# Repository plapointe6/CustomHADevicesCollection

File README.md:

# Custom Home Assistant devices collection

This repo contain custom IOT devices developped to work with ESP8266/ESP32, MQTT and Home Assistant.

# Required arduino libraries

Most of the devices needs these arduino libraries to work : 
 - https://github.com/plapointe6/EspMQTTClient
 - https://github.com/plapointe6/HAMqttDevice
 - https://github.com/jwrw/ESP_EEPROM

# Required Home Assistant parameters

Home Assistant must be communicating with an MQTT broker.
Here is the suggested configuration in `configuration.yaml` : 

```yaml
mqtt:
  broker: broker ip here
  username: username here
  password: password here
  discovery: true
  discovery_prefix: ha
  birth_message:
    topic: 'ha/status'
    payload: 'online'
    retain: true
  will_message:
    topic: 'ha/status'
    payload: 'offline'
    retain: true
```

# Architecture

These devices take advantages of MQTT discovery in Home Assistant. No manual steps are needed to add these devices in Home Assistant. Also, with the provided code, if something goes wrong (Wifi goes down, MQTT goes down, etc.) everything will reconnect automatically whitout your intervention.

Nothing is retained with MQTT (except for the HA status) and no device use the optimistic mode.

## Message types

There is three messages types when communicating with Home Assitant via MQTT.
- Configuration: these messages register your device into HA with MQTT discovery. all details/config of the device are sent with this message. It is the first thing you have to send to HA.
- State: this contain the current state of the device. For a light, the state will be either "ON" or "OFF".
- Command: this contains a resquest to change the state of the device. Wen receiving that, we do the necessary to update the device (ex: close/open the light) and send back the confirmation to Home Assistant when it's done by sending the new state.
- Attributes: Custom device attributes that can be sent to Home Assitant. These attributes will be displayed in the device card.
- Home assistant status: this is a retained message and contains the state of HA, either "online" or "offline".

## Devices events chronology

1. setup(): initilisations, load the previous state from EEPROM, configure the MQTT device.
2. onConnectionEstablished(): this callback is called each time everything get up and running (MQTT connection and WiFi connection). Here we subscribe to commands topics and Home assistant status.
3. We receive a Home Assistant status message indicating that HA is online. Then, we register the device to HA by sending the configuration message. After that, we needs to wait a little to let HA register and activate the device (wait five seconds)
4. When the waiting time as ended, we send the current device state to HA. This will update the device state in HA to match what was saved into EEPROM. Also, the attributes of the device are initialised with the IP address of the device and are sent to Home assistant.

I recommend taking a look to the onoff_light code to see these concepts in action.

## Web updater

Each device host a web updater that can be accessed with your browser by typing the ip address or the name of the device. The default username/password will be the same as your MQTT username/password.

# Add yours

If you successfully develop a new MQTT device based on these exemples (ESPMQTTClient/HAMqttDevice), create a pull request, everyones will benefit :)

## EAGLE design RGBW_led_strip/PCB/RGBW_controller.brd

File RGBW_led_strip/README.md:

# RGBW led strip controller

This device use a ESP8266 (Wemos D1 Mini) in pair with 4 MOSFET to control an RGBW led strip via PWM.

## BOM

- 1x Wemos D1 Mini
- 4x Mosfet - IRLB8721
- 1x Voltage regulator - [Mini DC-DC Converter Adjustable Power Supply Step Down Module](https://www.banggood.com/5Pcs-Mini-DC-DC-Converter-Adjustable-Power-Supply-Step-Down-Module-p-951165.html?rmmds=myorder&cur_warehouse=CN)
- 4x Resistor - 100ohm
- 1x Dc power jack

## Schematics

## Software

The software uses the EspMQTTClient, HAMQTTDevice and ESP_EEPROM libraries. You can find the arduino sketch in the "RGBW_led_strip" folder.

## PCB and 3D printed case

For a more finished product, milling your own PCB and enclosing the electronics into a case would be great.

You will find the .stl files in the "3D printed case" folder and the PCB for milling in the "PCB" folder.

DISCLAIMER: I was pretty new to electronics when a created this device, use at your own risk.

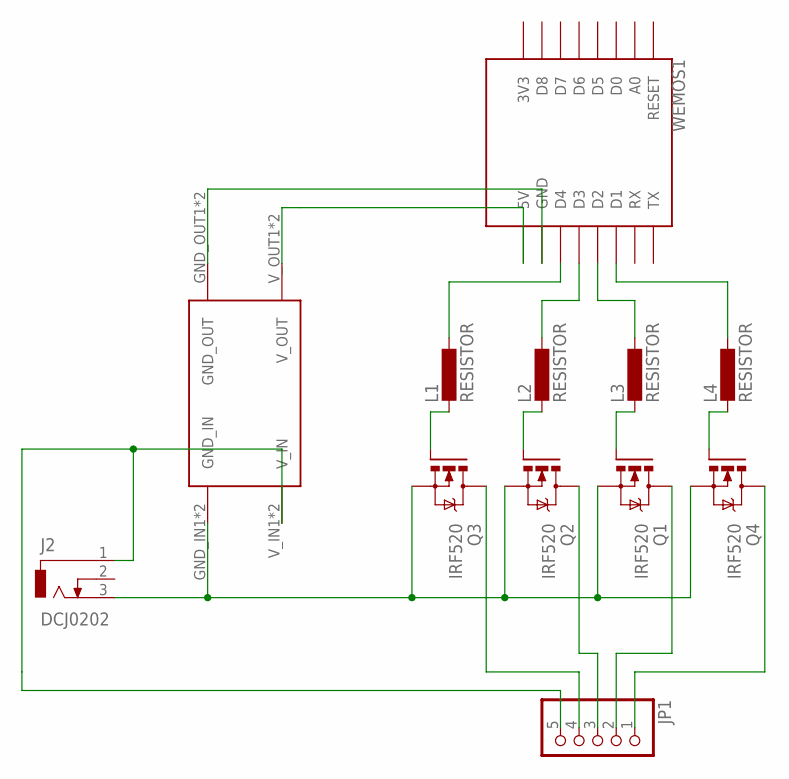
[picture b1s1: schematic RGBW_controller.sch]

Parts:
J2: DCJ0202
JP1: PINHD-1X5; 1X05
L1, L2, L3, L4: RESISTOR
Q1, Q2, Q3, Q4: IRF520; TO220BV
U$1: DC-DC-CONVERTER
WEMOS1: WEMOS-D1-MINI

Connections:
unnamed: L4.2, Q4.G
unnamed: J2.3, Q1.S, Q2.S, Q3.S, Q4.S, U$1.GND_IN1 (GND_IN), U$1.GND_IN2 (GND_IN)
unnamed: JP1.4, Q3.D
unnamed: J2.1, JP1.5, U$1.V_IN1 (V_IN), U$1.V_IN2 (V_IN)
unnamed: L1.2, Q3.G
unnamed: L2.2, Q2.G
unnamed: L3.2, Q1.G
unnamed: L4.1, WEMOS1.D1
unnamed: L3.1, WEMOS1.D2
unnamed: L2.1, WEMOS1.D3
unnamed: L1.1, WEMOS1.D4
unnamed: U$1.V_OUT1 (V_OUT), U$1.V_OUT2 (V_OUT), WEMOS1.5V
unnamed: U$1.GND_OUT1 (GND_OUT), U$1.GND_OUT2 (GND_OUT), WEMOS1.GND
unnamed: JP1.3, Q2.D
unnamed: JP1.2, Q1.D
unnamed: JP1.1, Q4.D

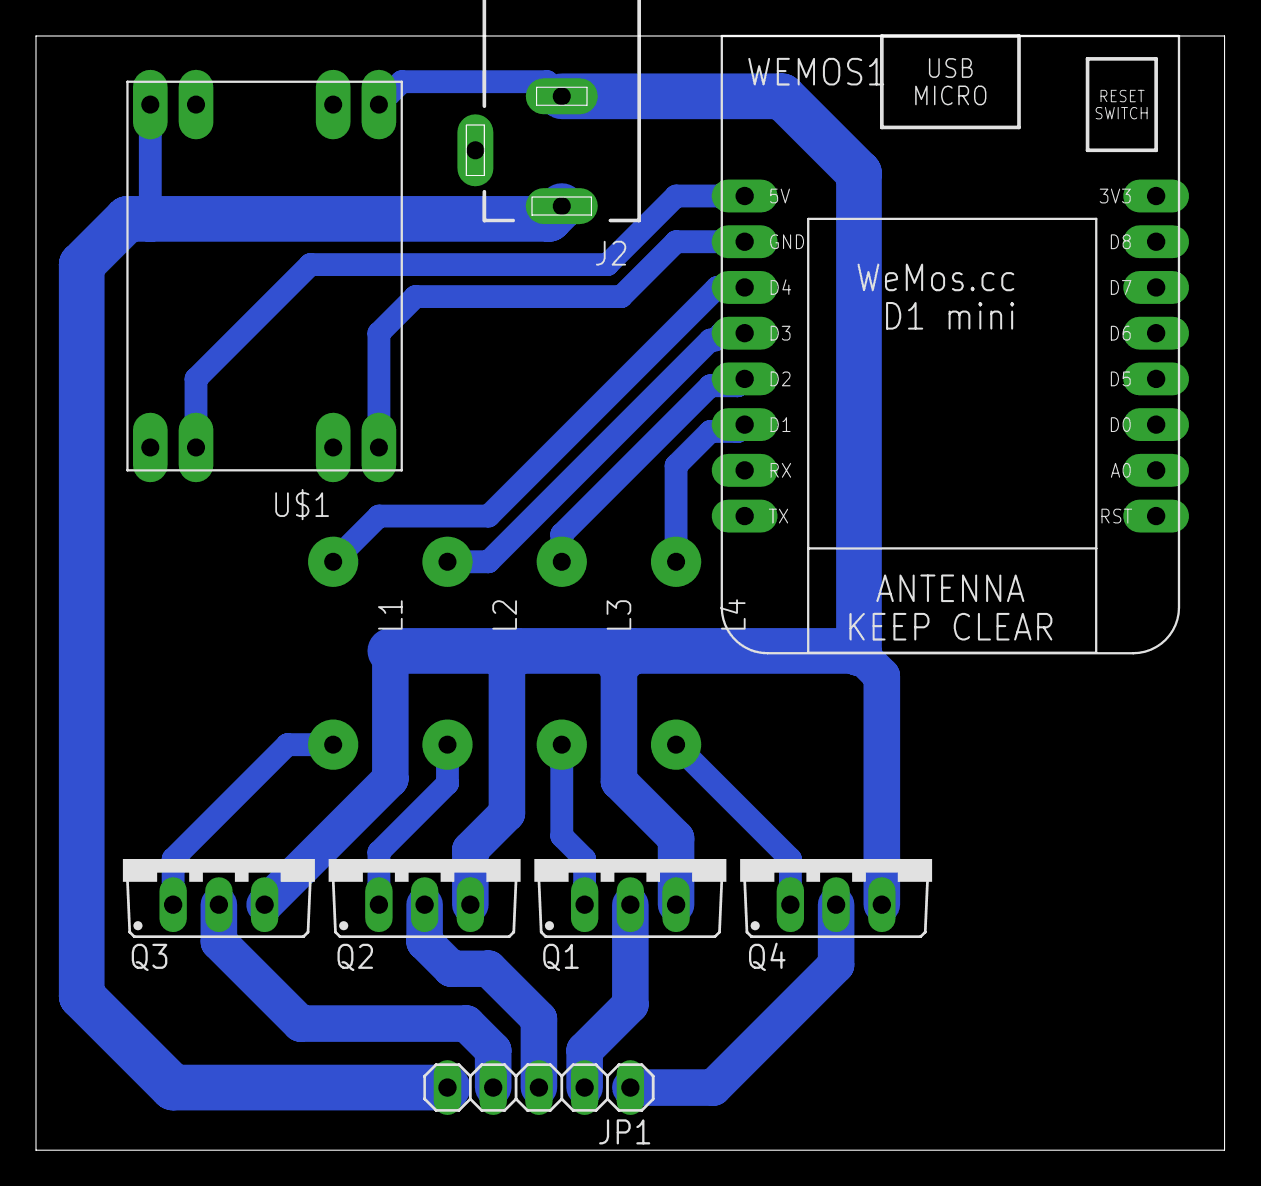
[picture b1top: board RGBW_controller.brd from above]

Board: 2 copper layers, 66.0 x 61.9 mm, 12 parts (0 on the bottom side), 16 nets.

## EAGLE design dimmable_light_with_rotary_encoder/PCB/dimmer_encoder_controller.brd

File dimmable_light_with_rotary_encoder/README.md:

# Dimmable light with rotary encoder control

This device use a ESP8266 (Wemos D1 Mini) in pair with a rotary encoder and a MOSFET to control a light via PWM. In my case, the light is a warm white led strip, but any device controllable via PWM could work (unless it draws too much amps).

## BOM

- 1x Wemos D1 Mini
- 1x Mosfet - IRLB8721
- 1x Voltage regulator - [Mini DC-DC Converter Adjustable Power Supply Step Down Module](https://www.banggood.com/5Pcs-Mini-DC-DC-Converter-Adjustable-Power-Supply-Step-Down-Module-p-951165.html?rmmds=myorder&cur_warehouse=CN)
- 1x Rotary encoder - 5pins, 11mm x 15mm - [like this one](https://www.banggood.com/10Pcs-15mm-Rotary-Encoder-Switch-with-Key-Switch-with-2-Bit-Gray-Scale-Micro-Switch-p-1593839.html?rmmds=search&cur_warehouse=CN)
- 1x Resistor - 100ohm
- 2x Dc power jack

## Schematics

## Software

The software uses the EspMQTTClient, HAMQTTDevice and ESP_EEPROM libraries. You can find the arduino sketch in the "dimmable_light_rotary_encoder" folder.

## PCB and 3D printed case

For a more finished product, milling your own PCB and enclosing the electronics into a case would be great.

You will find the .stl files in the "3D printed case" folder and the PCB for milling in the "PCB" folder.

DISCLAIMER: I was pretty new to electronics when a created this device, use at your own risk.

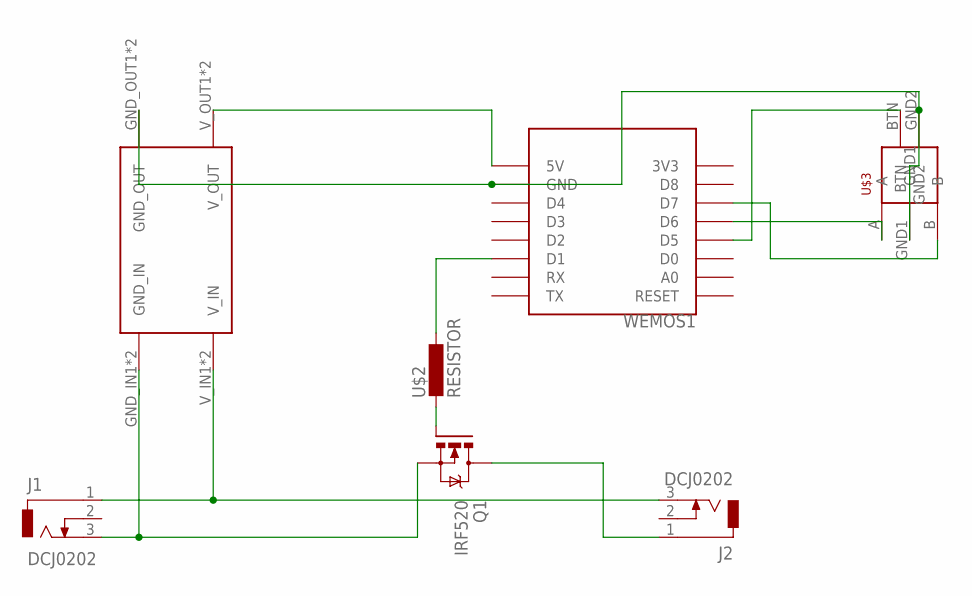
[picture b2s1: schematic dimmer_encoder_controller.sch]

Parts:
J1, J2: DCJ0202
Q1: IRF520; TO220BV
U$1: DC-DC-CONVERTER
U$2: RESISTOR
U$3: ROTARY_ENCODER
WEMOS1: WEMOS-D1-MINI

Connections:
unnamed: Q1.G, U$2.2
unnamed: U$1.V_OUT1 (V_OUT), U$1.V_OUT2 (V_OUT), WEMOS1.5V
unnamed: U$1.GND_OUT1 (GND_OUT), U$1.GND_OUT2 (GND_OUT), U$3.GND1, U$3.GND2, WEMOS1.GND
unnamed: U$2.1, WEMOS1.D1
unnamed: J1.1, J2.3, U$1.V_IN1 (V_IN), U$1.V_IN2 (V_IN)
unnamed: J1.3, Q1.S, U$1.GND_IN1 (GND_IN), U$1.GND_IN2 (GND_IN)
unnamed: J2.1, Q1.D
unnamed: U$3.A, WEMOS1.D6
unnamed: U$3.B, WEMOS1.D7
unnamed: U$3.BTN, WEMOS1.D5

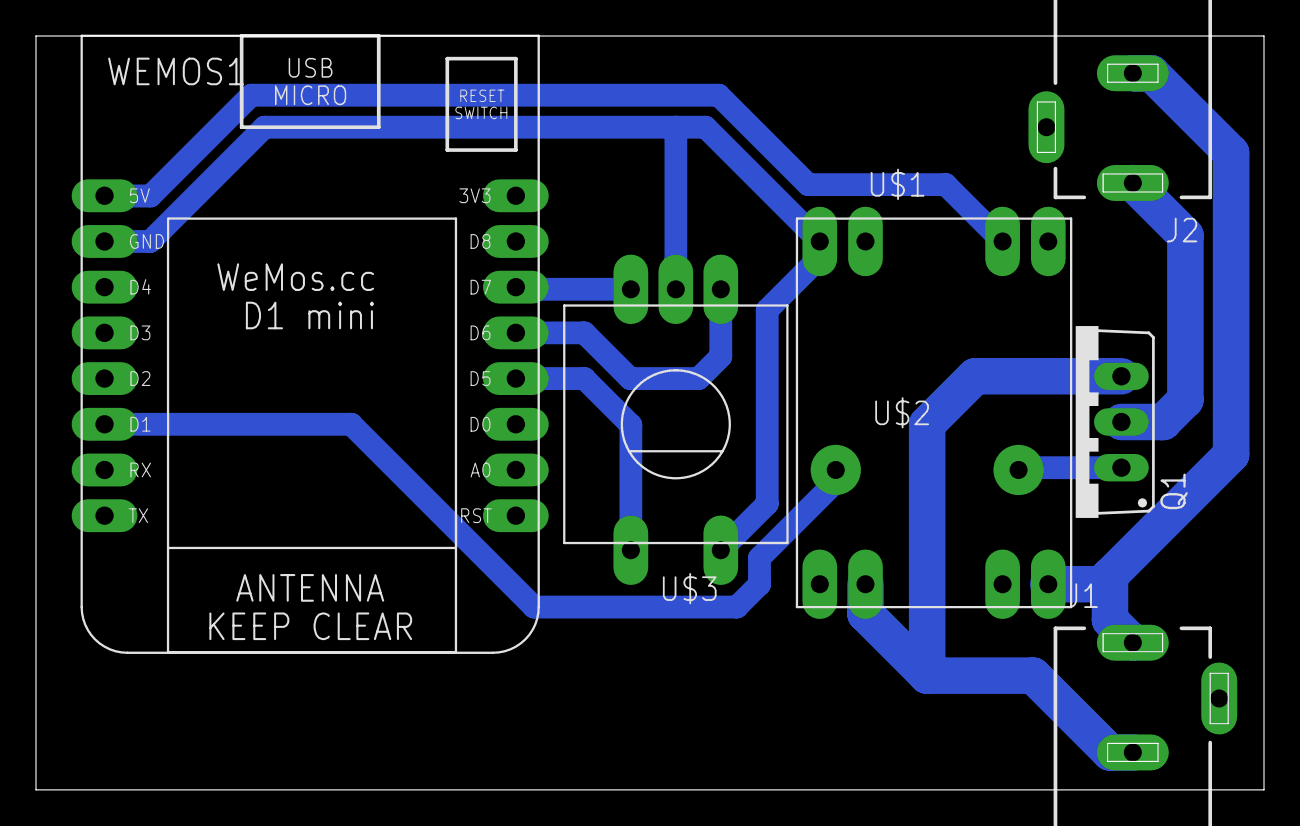
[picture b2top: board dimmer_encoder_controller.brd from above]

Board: 2 copper layers, 68.2 x 41.9 mm, 7 parts (0 on the bottom side), 10 nets.

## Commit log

2020-09-21 Add dimmable light, PCB and shematics coming soon
2020-09-21 Correct images
2020-10-18 Add dimmable light hardware
2020-10-19 Add RGBW strip
2020-10-19 Add shematics for RGBW strip
